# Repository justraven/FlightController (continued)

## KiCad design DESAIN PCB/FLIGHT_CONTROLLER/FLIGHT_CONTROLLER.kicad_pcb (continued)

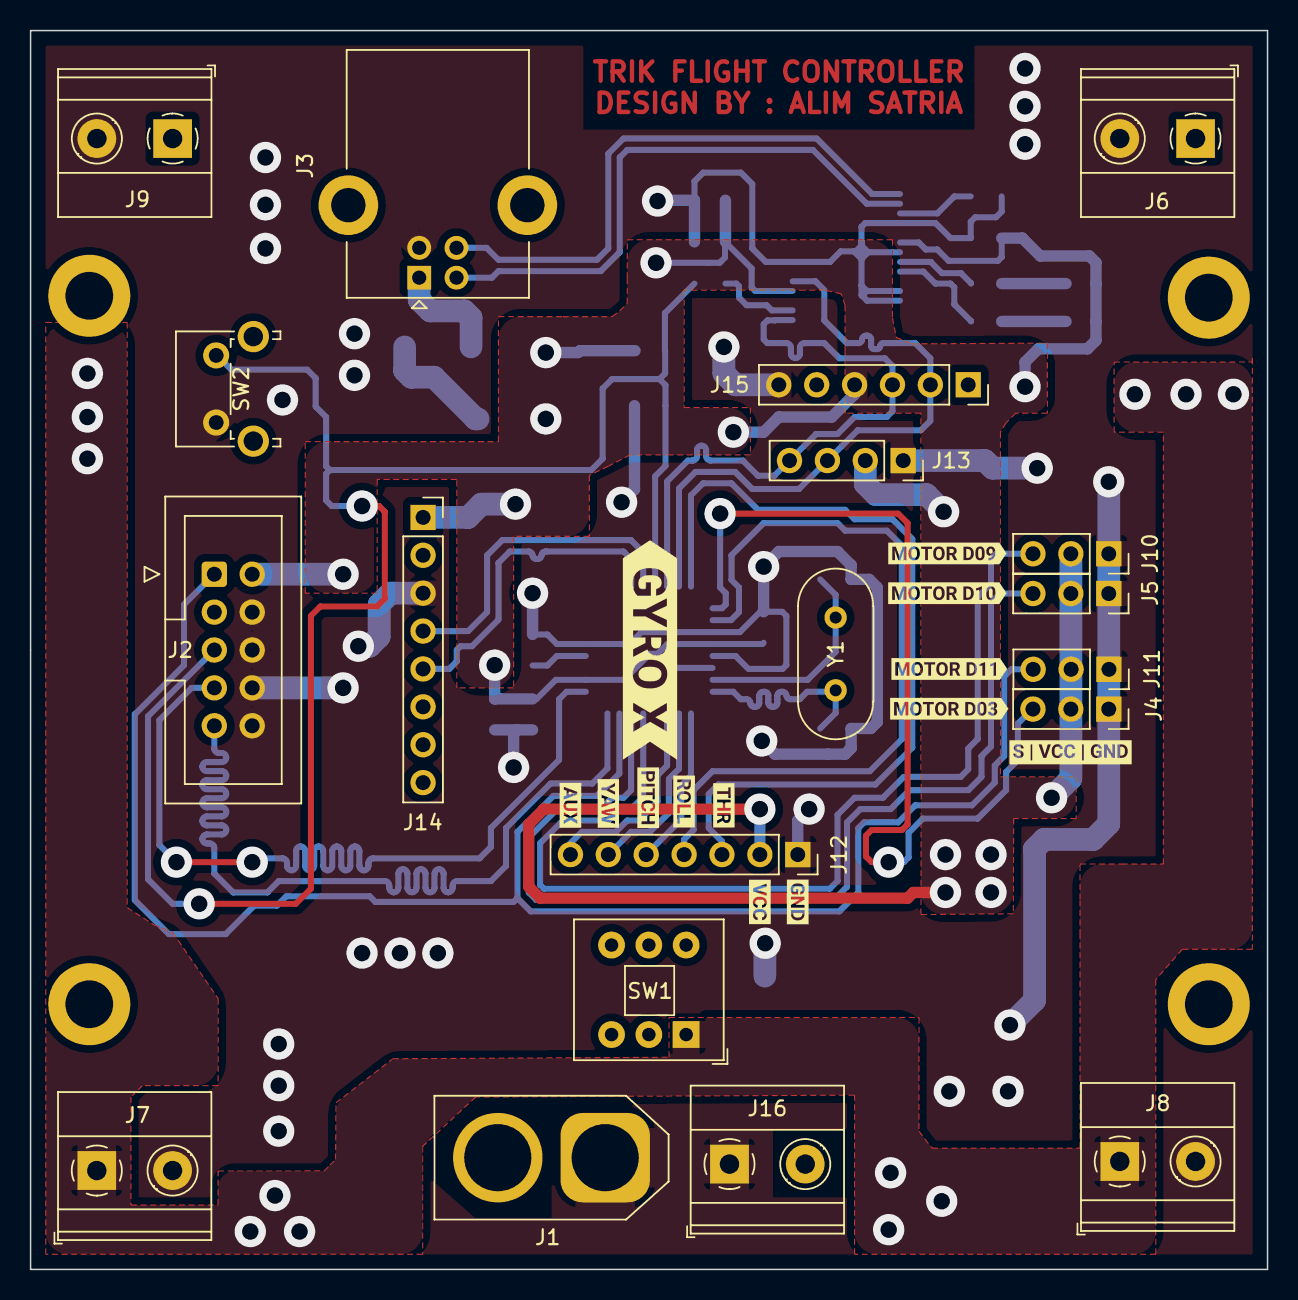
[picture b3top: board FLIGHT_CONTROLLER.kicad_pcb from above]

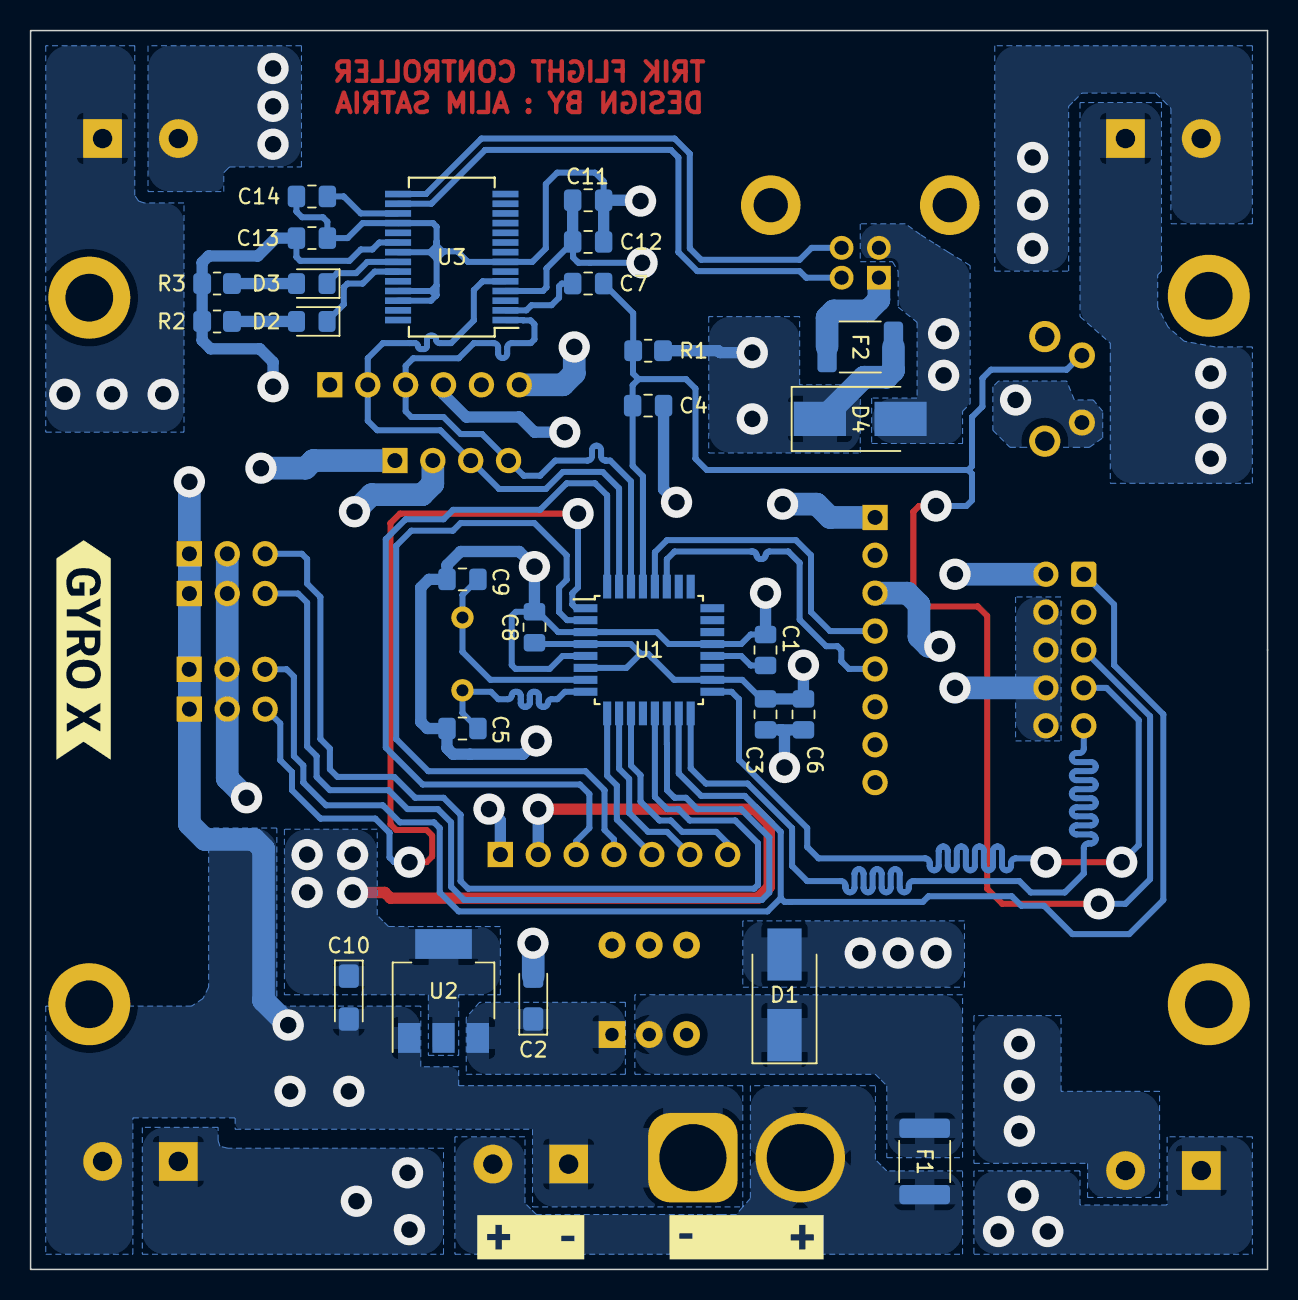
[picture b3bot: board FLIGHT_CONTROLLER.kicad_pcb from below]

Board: 2 copper layers, 82.9 x 83.1 mm, 65 parts (29 on the bottom side), 33 nets.

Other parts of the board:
kibuzzard-63DE9C89: G***; kibuzzard-63DE9C89
kibuzzard-63DE9C99: G***; kibuzzard-63DE9C99
kibuzzard-63DE9E57: G***; kibuzzard-63DE9E57
kibuzzard-63DE9E82: G***; kibuzzard-63DE9E82
kibuzzard-63DE9F2F: G***; kibuzzard-63DE9F2F
kibuzzard-63DE9F75: G***; kibuzzard-63DE9F75
kibuzzard-63DE9FCF: G***; kibuzzard-63DE9FCF
kibuzzard-63DEA0F2: G***; kibuzzard-63DEA0F2
kibuzzard-63DEA11E: G***; kibuzzard-63DEA11E
kibuzzard-63DEA12D: G***; kibuzzard-63DEA12D
kibuzzard-63DEA114: G***; kibuzzard-63DEA114
kibuzzard-63DEA138: G***; kibuzzard-63DEA138
kibuzzard-63E733C3: G***; kibuzzard-63E733C3
kibuzzard-63E734BE: G***; kibuzzard-63E734BE
kibuzzard-63E7341A: G***; kibuzzard-63E7341A
kibuzzard-63E7348F: G***; kibuzzard-63E7348F

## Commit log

2023-01-22 add Desain PCB
2023-01-24 update PCB schematic
2023-01-26 complete schematic
2023-01-30 add PCB file
2023-02-02 [Board] almost complete
2023-02-02 [Broad] just need to route PWM signal
2023-02-04 [Board] complete, need review
2023-02-04 [Board] Review complete
2023-02-07 [board] complete
2023-02-12 [board] correction
2023-03-03 add PCB V.1.2
2023-03-05 add PCB REV 2
2023-03-08 backup files
2023-03-10 backup
2023-06-05 add new files
    - more documentation files for PCB Rev 2
    - add PCB Rev 3
    - add 3D Models
